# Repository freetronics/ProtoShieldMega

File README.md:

Freetronics ProtoShield Mega U
==============================
Copyright 2011 Freetronics Pty Ltd  
Freetronics site:  <www.freetronics.com>  
Freetronics email: <info@freetronics.com>  

A special-purpose prototyping shield designed to stack on the
Freetronics EtherMega, designed to clear the PoE Regulator Module
fitted on top of the host board.

Features:

 * Special clearance area for PoE Regulator board.
 * Parts overlay on both the top and the bottom so you can see what you
   are connecting without having to keep turning the board over.

More information is available at:

  http://www.freetronics.com/psmu

The "docs" folder within this repository includes a handy copy of the
schematic in PDF format and image(s) of the pcb.

INSTALLATION
------------
The design is saved as an EAGLE project. EAGLE PCB design software is
available from www.cadsoftusa.com free for non-commercial use. To use
this project download it and place the directory containing these files
into the "eagle" directory on your computer. Then open EAGLE and
navigate to Projects -> eagle -> ProtoShieldMegaU.

DISTRIBUTION
------------
The specific terms of distribution of this project are governed by the
license referenced below.

LICENSE
-------
Licensed under the TAPR Open Hardware License (www.tapr.org/OHL).
The "license" folder within this repository also contains a copy of
this license in plain text format.

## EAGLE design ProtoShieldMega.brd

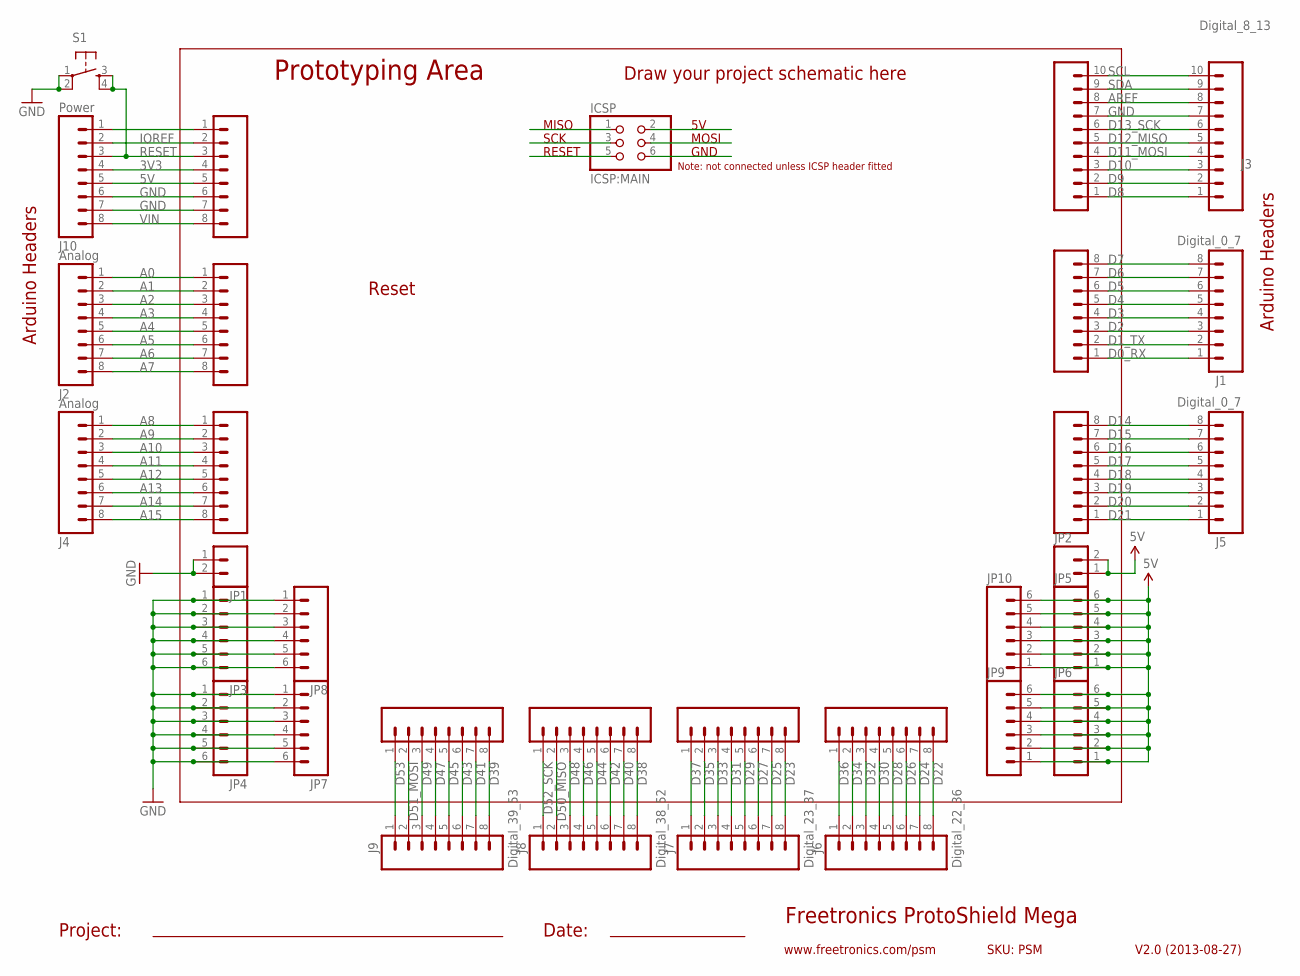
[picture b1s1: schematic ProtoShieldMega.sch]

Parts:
ICSP: ICSP:MAIN; 2X03
J1, J5: Digital_0_7; 1X08
J2, J4: Analog; 1X08
J3: Digital_8_13; 1X10
J6: Digital_22_36; 1X08
J7: Digital_23_37; 1X08
J8: Digital_38_52; 1X08
J9: Digital_39_53; 1X08
J10: Power; 1X08
JP1, JP2: M02PTH; 1X02
JP3, JP4, JP5, JP6, JP7, JP8, JP9, JP10: M06SIP; 1X06
S1: TAC_SWITCHPTH; TACTILE-PTH
SL1, SL5, SL6, SL7, SL8, SL9: Digital_0_7; 1X08
SL2, SL4: Analog; 1X08
SL3: Digital_8_13; 1X10
SLP: Power; 1X08

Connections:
3V3: J10.4, SLP.4
5V: J10.5, JP2.1, JP2.2, JP5.1, JP5.2, JP5.3, JP5.4, JP5.5, JP5.6, JP6.1, JP6.2, JP6.3, JP6.4, JP6.5, JP6.6, JP9.1, JP9.2, JP9.3, JP9.4, JP9.5, JP9.6, JP10.1, JP10.2, JP10.3, JP10.4, JP10.5, JP10.6, SLP.5
A0: J2.1, SL2.1
A1: J2.2, SL2.2
A2: J2.3, SL2.3
A3: J2.4, SL2.4
A4: J2.5, SL2.5
A5: J2.6, SL2.6
A6: J2.7, SL2.7
A7: J2.8, SL2.8
A8: J4.1, SL4.1
A9: J4.2, SL4.2
A10: J4.3, SL4.3
A11: J4.4, SL4.4
A12: J4.5, SL4.5
A13: J4.6, SL4.6
A14: J4.7, SL4.7
A15: J4.8, SL4.8
AREF: J3.8, SL3.8
D0_RX: J1.1, SL1.1
D1_TX: J1.2, SL1.2
D2: J1.3, SL1.3
D3: J1.4, SL1.4
D4: J1.5, SL1.5
D5: J1.6, SL1.6
D6: J1.7, SL1.7
D7: J1.8, SL1.8
D8: J3.1, SL3.1
D9: J3.2, SL3.2
D10: J3.3, SL3.3
D11_MOSI: J3.4, SL3.4
D12_MISO: J3.5, SL3.5
D13_SCK: J3.6, SL3.6
D14: J5.8, SL5.8
D15: J5.7, SL5.7
D16: J5.6, SL5.6
D17: J5.5, SL5.5
D18: J5.4, SL5.4
D19: J5.3, SL5.3
D20: J5.2, SL5.2
D21: J5.1, SL5.1
D22: J6.8, SL6.8
D23: J7.8, SL7.8
D24: J6.7, SL6.7
D25: J7.7, SL7.7
D26: J6.6, SL6.6
D27: J7.6, SL7.6
D28: J6.5, SL6.5
D29: J7.5, SL7.5
D30: J6.4, SL6.4
D31: J7.4, SL7.4
D32: J6.3, SL6.3
D33: J7.3, SL7.3
D34: J6.2, SL6.2
D35: J7.2, SL7.2
D36: J6.1, SL6.1
D37: J7.1, SL7.1
D38: J8.8, SL8.8
D39: J9.8, SL9.8
D40: J8.7, SL8.7
D41: J9.7, SL9.7
D42: J8.6, SL8.6
D43: J9.6, SL9.6
D44: J8.5, SL8.5
D45: J9.5, SL9.5
D46: J8.4, SL8.4
D47: J9.4, SL9.4
D48: J8.3, SL8.3
D49: J9.3, SL9.3
D50_MISO: J8.2, SL8.2
D51_MOSI: J9.2, SL9.2
D52_SCK: J8.1, SL8.1
D53: J9.1, SL9.1
GND: J3.7, J10.6, J10.7, JP1.1, JP1.2, JP3.1, JP3.2, JP3.3, JP3.4, JP3.5, JP3.6, JP4.1, JP4.2, JP4.3, JP4.4, JP4.5, JP4.6, JP7.1, JP7.2, JP7.3, JP7.4, JP7.5, JP7.6, JP8.1, JP8.2, JP8.3, JP8.4, JP8.5, JP8.6, S1.1, S1.2, SL3.7, SLP.6, SLP.7
IOREF: J10.2, SLP.2
unnamed: J10.1, SLP.1
RESET: J10.3, S1.3, S1.4, SLP.3
SCL: J3.10, SL3.10
SDA: J3.9, SL3.9
VIN: J10.8, SLP.8

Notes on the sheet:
Freetronics ProtoShield Mega
V2.0 (2013-08-27)
www.freetronics.com/psm
SKU: PSM
Prototyping Area
Arduino Headers
Project:
Date:
Draw your project schematic here
Reset
GND
MISO
RESET
SCK
MOSI
Note: not connected unless ICSP header fitted

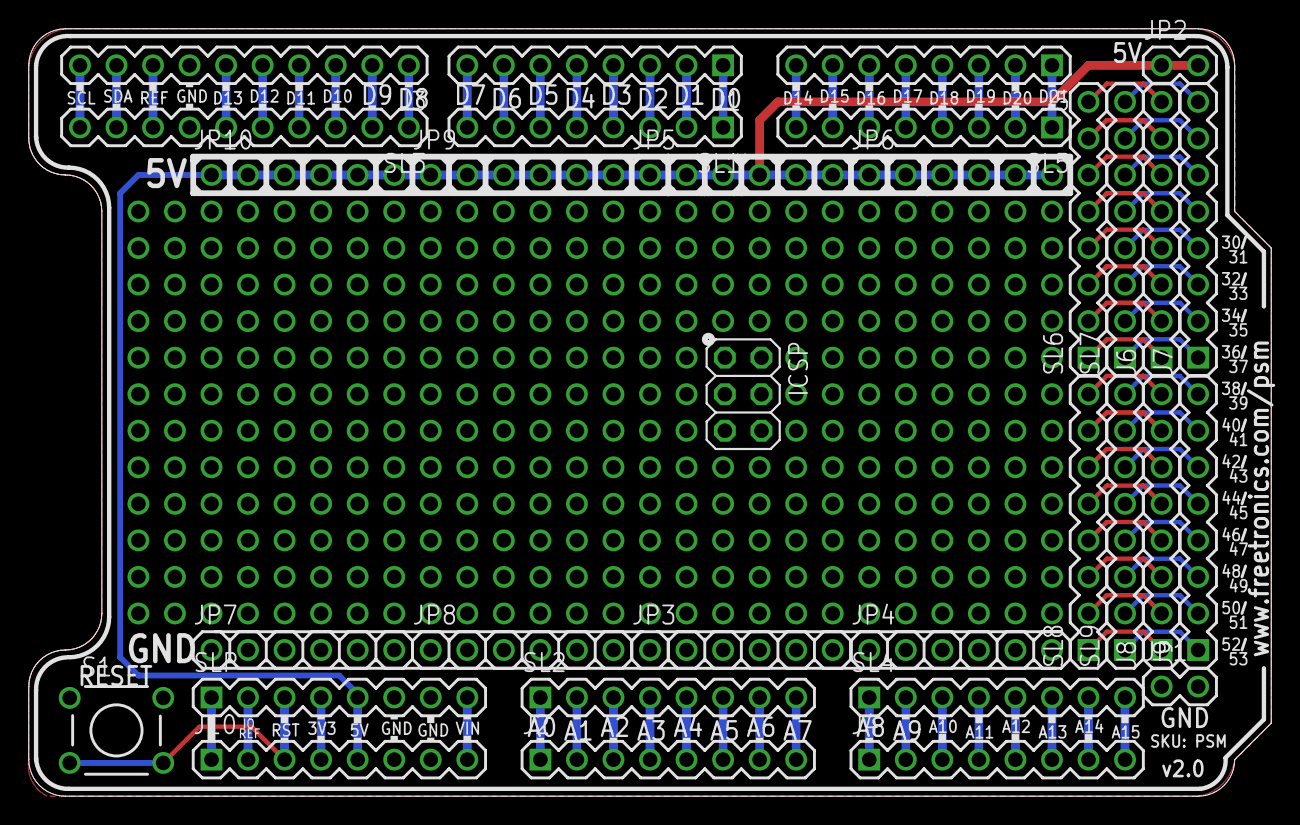
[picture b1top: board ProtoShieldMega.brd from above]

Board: 2 copper layers, 86.4 x 53.3 mm, 32 parts (0 on the bottom side), 80 nets.

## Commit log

2011-08-07 First version of project
2012-02-26 Routing and overlay. Still need to add ICSP header
2012-03-27 Added license files
2012-03-27 Improved overlay
2012-03-30 Production release v1_0
2013-03-13 Update to EAGLE 6 format
2013-03-14 Update for Arduino R3 headers
2013-08-28 Updated to R3 headers for v2.0 release
2013-08-28 Updated PDF of schematic for v2.0 release

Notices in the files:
ProtoShieldMega.brd:
(C) 2013
